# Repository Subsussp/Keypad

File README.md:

## Info

> It's just a simple macropad and i don't wanna mess it up so i kept it as it is simple and i wanna try to get this!!

> I dont wanna change or customize it i just wanna build it and see it work 

## Full Build

## Features 

> 6 switches with different functionalities (opening chrome for example)

> Rotary encoder to turn the volume up and down

## CAD Model:

## PCB

--------------------

## BOM:

Here is everything i need:

- Seeed XIAO RP2040 x1

- PCB x1

- Cherry MX switches x6

- Blank DSA keycaps x6

- SK6812 MINI Leds x2

- M3x16 Bolt x4

- M3 Heatset x4

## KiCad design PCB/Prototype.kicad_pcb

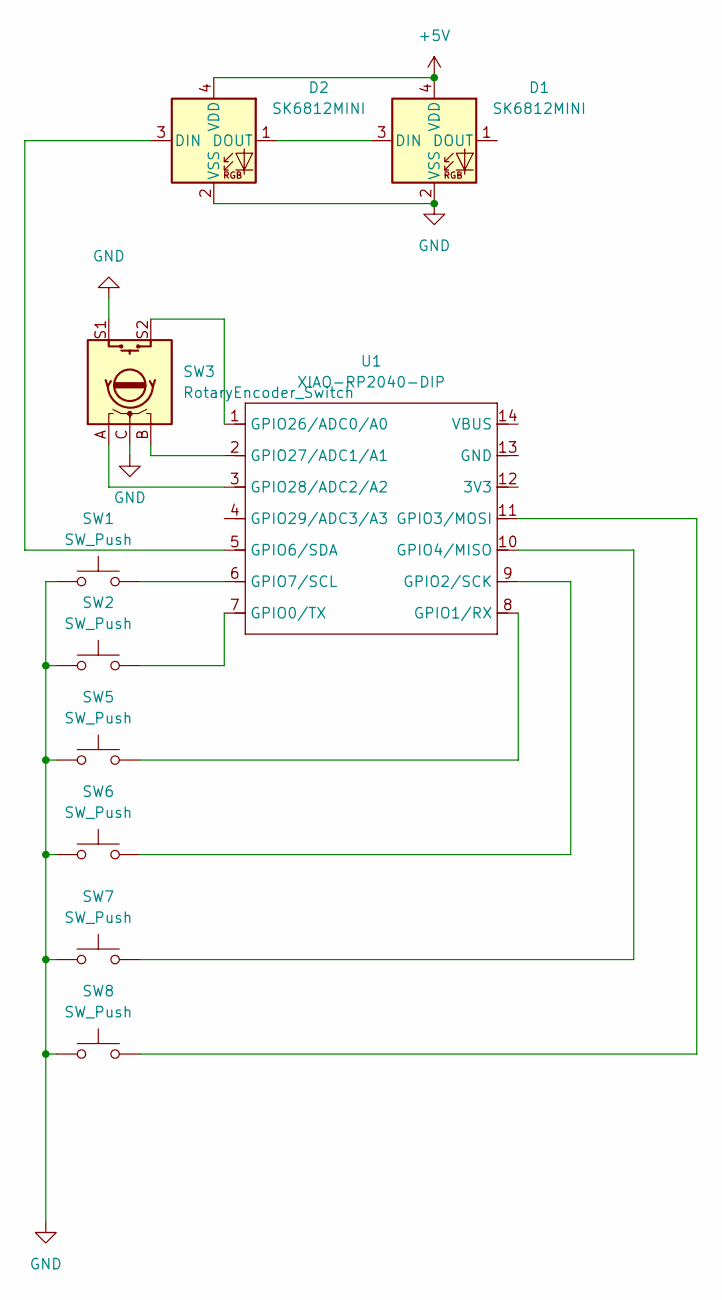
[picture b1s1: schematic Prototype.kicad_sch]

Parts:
D1, D2: SK6812MINI; LED_SK6812MINI_PLCC4_3.5x3.5mm_P1.75mm
SW1, SW2, SW5, SW6, SW7, SW8: SW_Push; SW_Cherry_MX_1.00u_PCB
SW3: RotaryEncoder_Switch; RotaryEncoder_Alps_EC11E-Switch_Vertical_H20mm
U1: XIAO-RP2040-DIP

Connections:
+5V: D1.4 (VDD), D2.4 (VDD)
GND: D1.2 (VSS), D2.2 (VSS), SW1.1, SW2.1, SW3.C, SW3.S1, SW5.1, SW6.1, SW7.1, SW8.1
unnamed: D1.3 (DIN), D2.1 (DOUT)
unnamed: D2.3 (DIN), U1.5 (GPIO6/SDA)
unnamed: SW2.2, U1.7 (GPIO0/TX)
unnamed: SW5.2, U1.8 (GPIO1/RX)
unnamed: SW6.2, U1.9 (GPIO2/SCK)
unnamed: SW8.2, U1.11 (GPIO3/MOSI)
unnamed: SW7.2, U1.10 (GPIO4/MISO)
unnamed: SW1.2, U1.6 (GPIO7/SCL)
unnamed: SW3.S2, U1.1 (GPIO26/ADC0/A0)
unnamed: SW3.B, U1.2 (GPIO27/ADC1/A1)
unnamed: SW3.A, U1.3 (GPIO28/ADC2/A2)

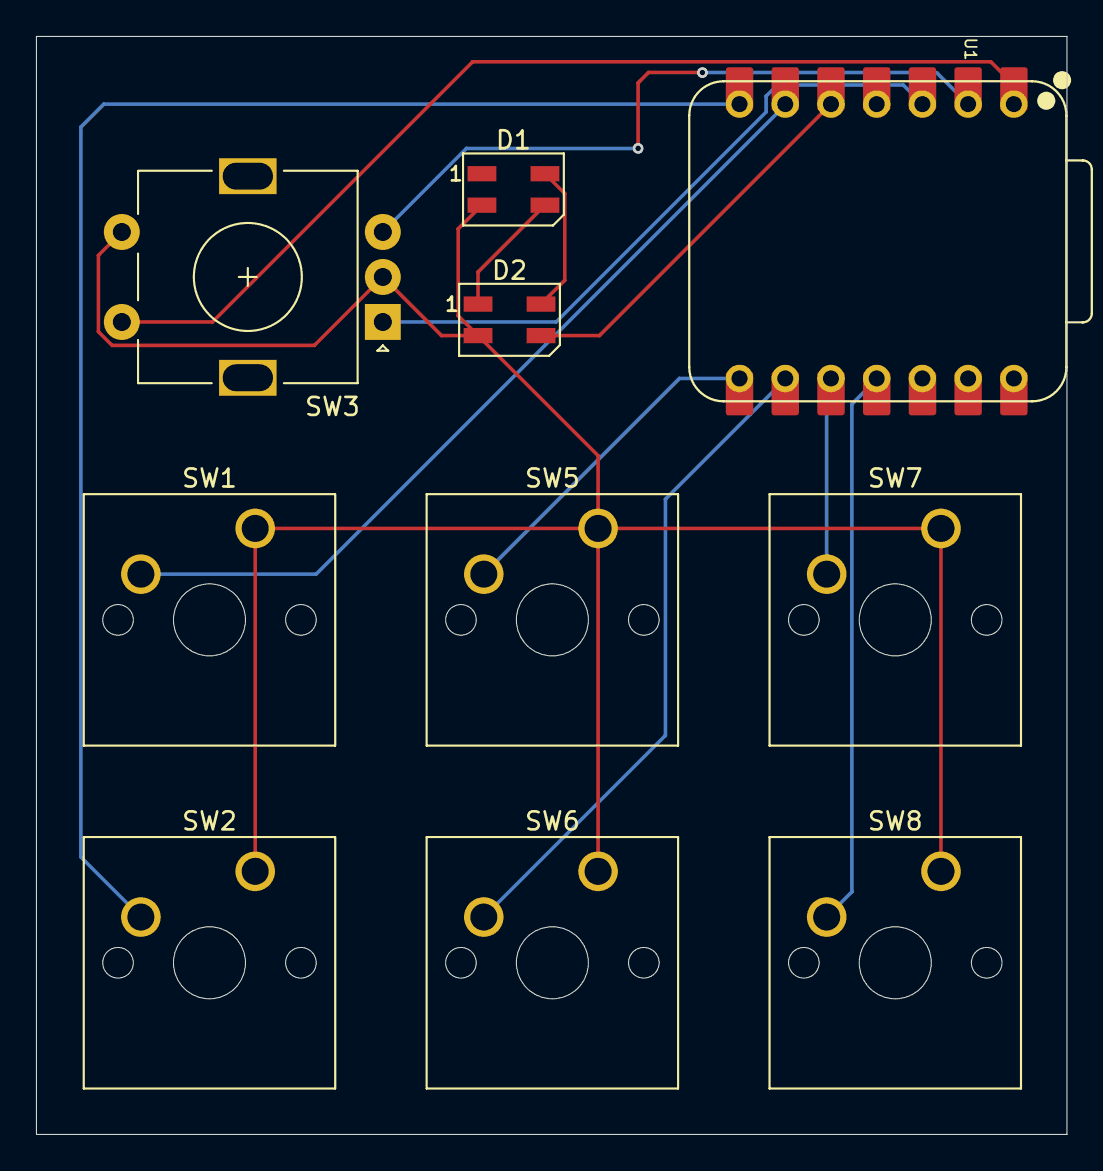
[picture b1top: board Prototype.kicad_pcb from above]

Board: 2 copper layers, 57.2 x 61.0 mm, 10 parts (0 on the bottom side), 13 nets.

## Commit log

2025-11-26 Initial commit!!
2025-11-27 Update CAD screenshot in README
2025-11-27 Rename CAD.png to CAD1.png
2026-01-26 Finished build
2026-01-28 Add screenshot to Full Build section in README
